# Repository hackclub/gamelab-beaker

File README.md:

# Game Lab Beaker
People learn best when they are making things that they are proud of, things that can share with others. We made [gamelab](https://github.com/hackclub/game-lab) to help facilitate this style of learning. People who have never written code before can use it to get started right away changing real code and eventually making their own games. The Beaker is a handheld console meant to further enhance and popularize this style of learning; we will send them to technical teenagers who make games to run on one, and they will be able to show their games running on this device to anyone.

https://user-images.githubusercontent.com/25539554/169143730-565797fc-a0e5-44eb-96f9-02093b27bbcb.mp4

Kaluma is a JS runtime implemented on top of JerryScript, which we've been extending with the parts of this project that require C optimization.

our fork:
https://github.com/hackclub/kaluma/tree/ced

the original repo:
https://github.com/kaluma-project/kaluma

## Upload Flow
Similar to [Kaluma's web IDE](https://kalumajs.org/ide/), one will be able to upload their games directly to the device through a web interface. That will be on the Game Lab repo.

## The Repo
We've been testing various runtimes and their hardware drivers as we make sure all of our components work and are configured correctly, hence `micropython_tests/` and `kaluma-tests/`. The file extension for the executables which run on these devices is `.uf2`, the `uf2/` folder contains the kaluma and micropython runtimes we've used to run the code in their respective files. This folder also contains `flash_nuke.uf2` which was compiled from a small C program designed to wipe the persistent memory on the chip, which is useful for recoverring from invalid states.

# Fear all ye who enter here
The remainder of the README is used for note taking, and is not intended to be particularly presentable.

### Parts

- Raspberry Pi Pico RP2040 PID: 4864
- 1.8" Color TFT LCD display with MicroSD Card Breakout - ST7735R PID: 358
- Adafruit I2S 3W Class D Amplifier Breakout - MAX98357A
- Mini Metal Speaker w/ Wires - 8 ohm 0.5W PID: 1890
- PowerBoost 1000 Charger - Rechargeable 5V Lipo USB Boost @ 1A - 1000C
- plus asorted switches and buttons

### Raspberry Pi Pico, rp2040

We're planning on using this chip.

Here is a [pinout diagram](https://datasheets.raspberrypi.com/pico/Pico-R3-A4-Pinout.pdf).

### Hooking Up the Screen, ST7735

We're planning on using [this screen](https://learn.adafruit.com/1-8-tft-display/breakout-pinouts).

This [video](https://www.youtube.com/watch?v=9rDXPcwuXLA) and [repo](https://github.com/stechiez/raspberrypi-pico) were very helpful in setting up the screen:

It uses this [version](https://www.banggood.in/1_44-Inch-TFT-SPI-Serial-Port-LCD-Module-Colorful-Screen-Display-Module-LCD-Screen-ST7735-Drive-p-1903603.html?warehouse=CN&ID=0&p=09122211383184201706&custlinkid=1784032&cur_warehouse=CN) of the screen. 

This [c library](https://github.com/bablokb/pico-st7735) may also be relevant.

Naming conventions vary slightly the below snippet from [this thread](https://forums.raspberrypi.com/viewtopic.php?t=212810) could help clear up some confusion here:

```
LED - GPIO18 - pin 12
SCK - GPIO11 - pin 23
SDA (MOSI) - GPIO10 - pin 19
A0 (D/C) - GPIO24 - pin 18
RESET - GPIO25 - pin 22
CS - GPIO8 - pin 24
GND - pin 6
VCC - pin 2
```

Other possibly useful links:

- https://helloraspberrypi.blogspot.com/2021/02/raspberry-pi-picomicropython-st7789-spi.html

### Kuluma

Instructions on how to build Kuluma.

https://github-wiki-see.page/m/kaluma-project/kaluma/wiki/Build

Which uses [Jerryscript](https://jerryscript.net/).

It has a [nice web IDE](https://kalumajs.org/ide/).

### Wiping Flash Memory

Load `flash_nuke.uf2` onto the Pico.

Can also refer to [this example](https://github.com/raspberrypi/pico-examples/blob/master/flash/nuke/nuke.c) from Raspberry Pi.

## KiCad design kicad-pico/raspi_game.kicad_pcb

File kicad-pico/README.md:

# raspi-game

Raspberry pi zero W based game console with:

- 3.7 Li-ion battery (+ buck/boost module)
- speaker (+ I2S module)
- D-pad and ABXY buttons
- 1.8" TFT screen
- type C USB for charging + serial port (CH340C)

## Front

## Back

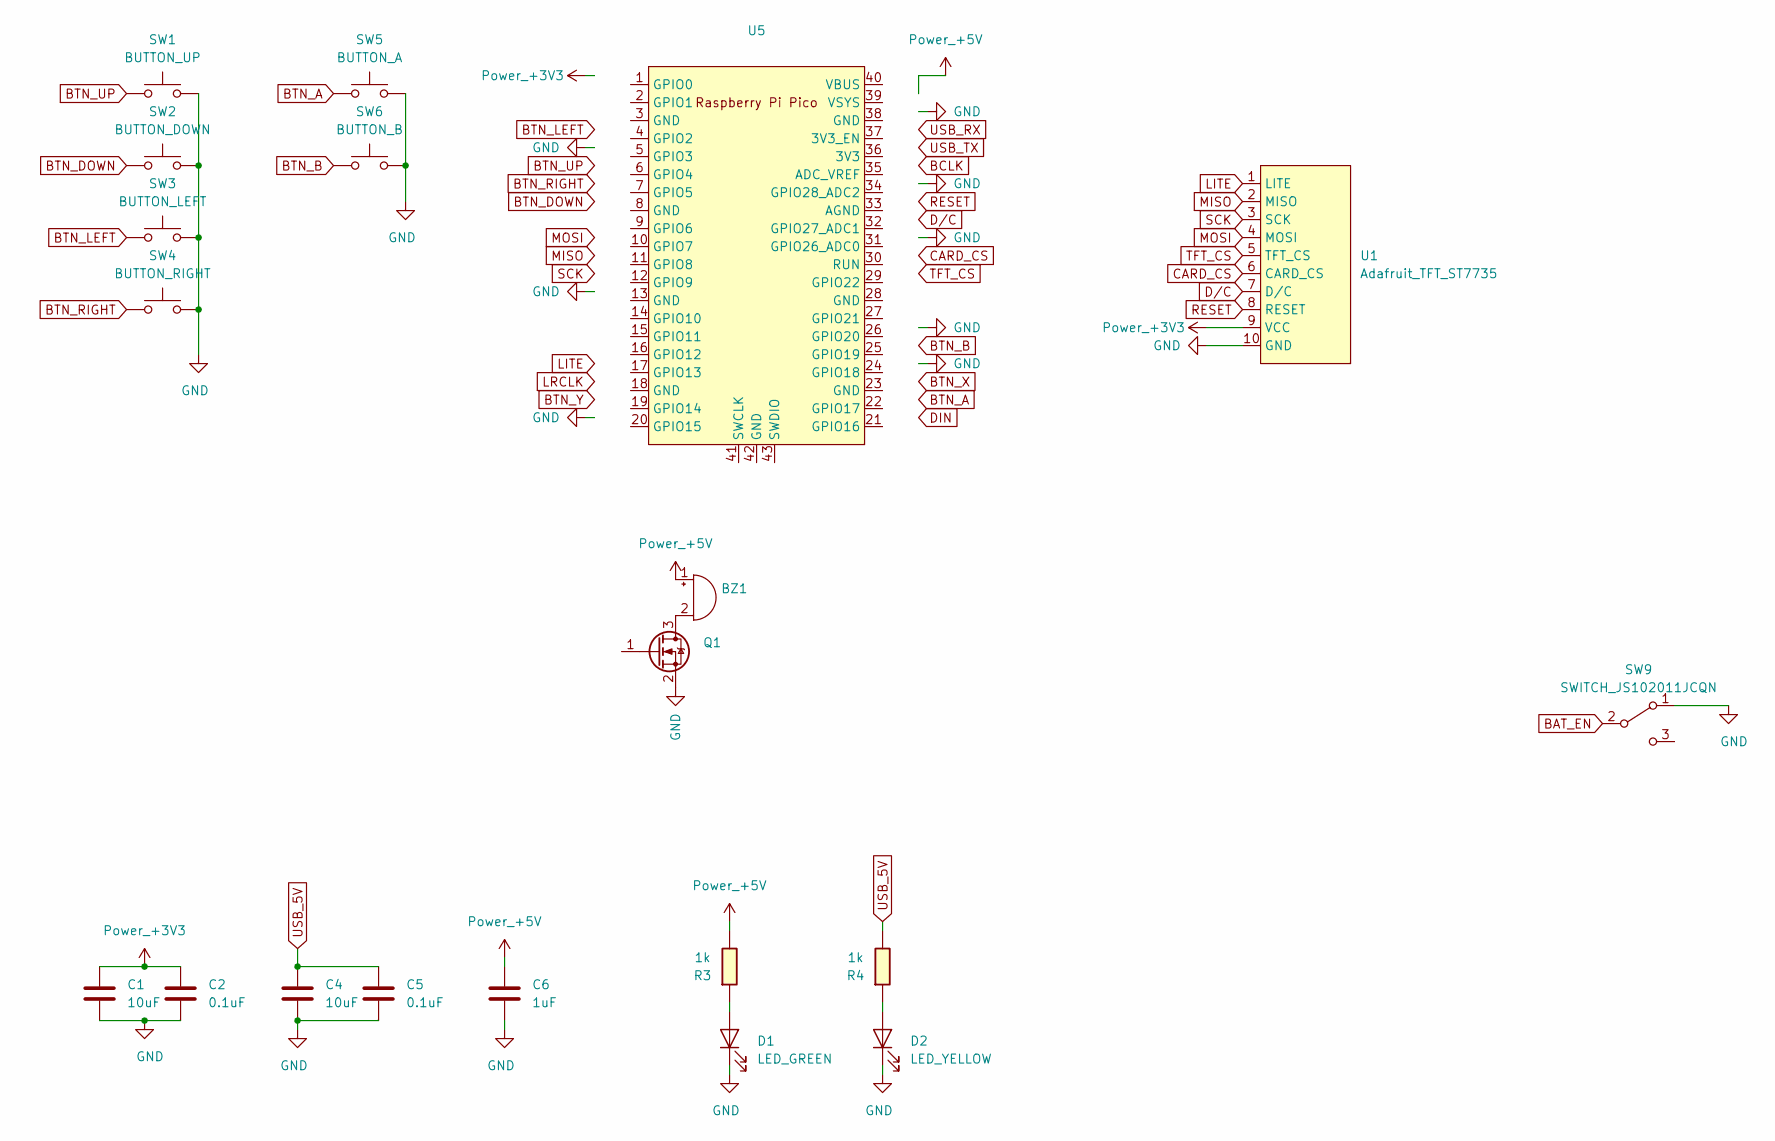
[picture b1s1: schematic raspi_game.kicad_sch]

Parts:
BZ1: (no value)
C1, C4: 10uF; C_1206
C2, C5: 0.1uF; C_1206
C6: 1uF; C_1206
D1: LED_GREEN; LED_1206
D2: LED_YELLOW; LED_1206
Q1: SOT-23
R3, R4: 1k; R_1206
SW1: BUTTON_UP; Button_Omron_B3SN_6x6mm
SW2: BUTTON_DOWN; Button_Omron_B3SN_6x6mm
SW3: BUTTON_LEFT; Button_Omron_B3SN_6x6mm
SW4: BUTTON_RIGHT; Button_Omron_B3SN_6x6mm
SW5: BUTTON_A; Button_Omron_B3SN_6x6mm
SW6: BUTTON_B; Button_Omron_B3SN_6x6mm
SW9: SWITCH_JS102011JCQN; Switch_SPDT_C&K_JS102011JCQN_9x3.6mm_P2.5mm
U1: Adafruit_TFT_ST7735
U5: (no value)

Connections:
+3V3: C1.1, C2.1, U1.9 (VCC)
+5V: BZ1.1 (-), C6.1, R3.1; also elsewhere on the board
BAT_EN: SW9.2 (B); also elsewhere on the board
BTN_A: SW5.1
BTN_B: SW6.1
BTN_DOWN: SW2.1
BTN_LEFT: SW3.1
BTN_RIGHT: SW4.1
BTN_UP: SW1.1
CARD_CS: U1.6 (CARD_CS)
D/C: U1.7 (D/C)
GND: C1.2, C2.2, C4.2, C5.2, C6.2, D1.1 (K), D2.1 (K), Q1.2 (S), SW1.2, SW2.2, SW3.2, SW4.2, SW5.2, SW6.2, SW9.1 (A), U1.10 (GND); also elsewhere on the board
LITE: U1.1 (LITE)
MISO: U1.2 (MISO)
MOSI: U1.4 (MOSI)
unnamed: BZ1.2 (+), Q1.3 (D)
unnamed: D1.2 (A), R3.2
unnamed: D2.2 (A), R4.2
RESET: U1.8 (RESET)
SCK: U1.3 (SCK)
TFT_CS: U1.5 (TFT_CS)
USB_5V: C4.1, C5.1, R4.1; also elsewhere on the board

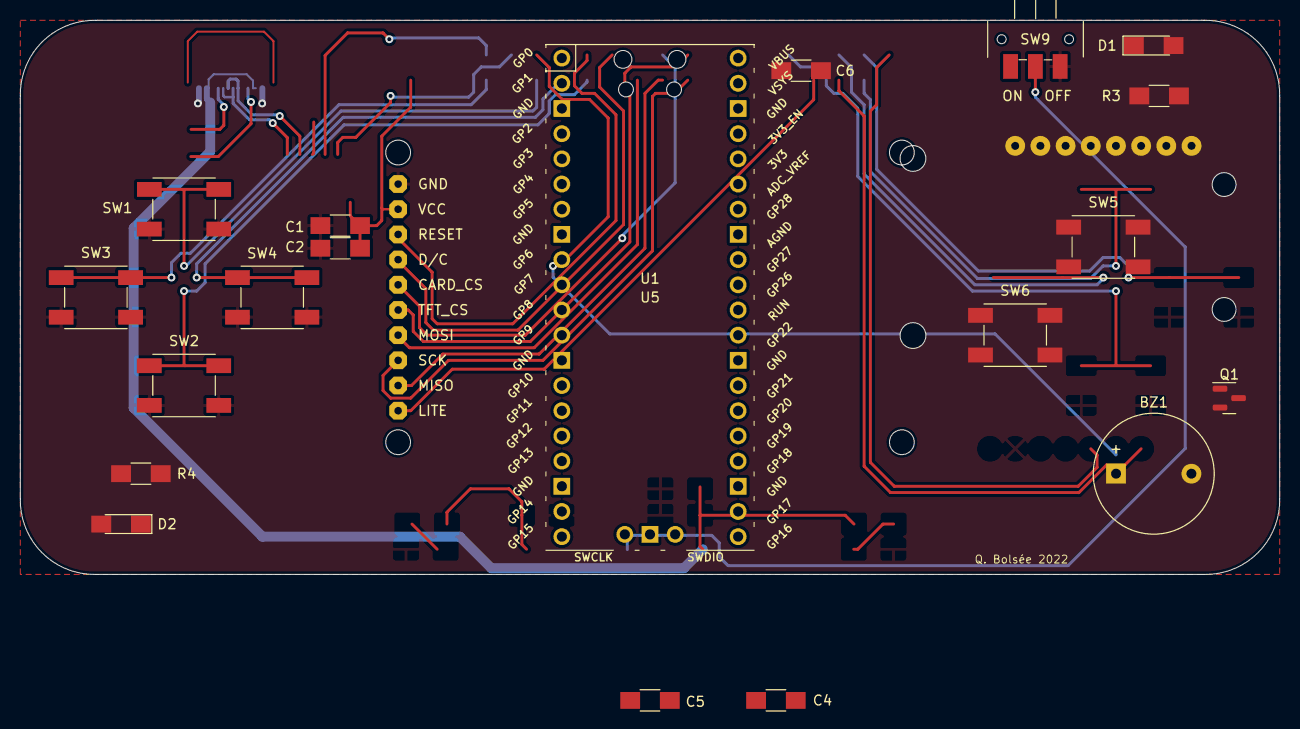
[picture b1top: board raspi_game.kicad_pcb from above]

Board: 2 copper layers, 127.0 x 55.9 mm, 21 parts (1 on the bottom side), 8 nets.

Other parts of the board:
U4: powerboost_1000C

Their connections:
+5V: U4.8 (OUT); also elsewhere on the board
BAT_EN: U4.4 (EN); also elsewhere on the board
GND: U4.5 (GND), U4.7 (GND); also elsewhere on the board
USB_5V: U4.1 (USB); also elsewhere on the board

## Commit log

2022-04-20 adding micropython screen code
2022-04-21 added kaluma screen drawing
2022-04-22 more drawing tests
2022-04-23 boosting baudrate
2022-04-25 added python button
2022-04-25 documentation updates
2022-04-27 Add drawing examples in both languages
2022-04-27 organization changes
2022-04-28 sprite jumps on platform
2022-04-29 more micropython tests
2022-05-03 dump screen buffer all at once
2022-05-12 adding sounds now
2022-05-13 finally a text based sprite
2022-05-13 hardcode less, suffer more
2022-05-13 okay yay
2022-05-16 run duck game!
2022-05-17 added kicad files
2022-05-18 updated kicad
2022-05-18 clean up readme
2022-05-18 Properly link in README
2022-05-18 Fix link
2022-05-18 add video of usage
2022-05-18 add note about upload flow
2022-05-18 reduce size of headers at bottom
2022-05-19 fix bug, run sokoban
